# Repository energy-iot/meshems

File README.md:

# MeshEMS Hardware

All files and documentation related to the MeshEMS hardware.

## Overview

The **NESL 865B EMS board** pairs an ESP32-S3 N16R8 (dual-core LX7, 16 MB flash, 8 MB PSRAM) with a purpose-built AC metering add-on and peripherals stack (Ethernet, SD Card reader, OLED display). For energy metering applications it supports either Modbus RTU energy meters (DDS238, CHD130, DDSU666 single-phase) or the CircuitSetup ATM90E32 6-channel SPI meter for 3-phase / multi-CT sites, in addition to the SHT20 temp/humidity sensor which communicates via Modbus. An optional external I2C PCF8574 8-channel SSR bank provide load-control outputs.

## Table of Contents

- [Board Diagrams](#board-diagrams)
- [Hardware Overview](#hardware-overview)
  - [Core Specifications](#core-specifications)
  - [RS-485 MODBUS RTU Module](#hw-519-breakout-rs-485-modbus-rtu-module)
  - [CANBUS V2.0 Interface](#mcp2515-breakout---canbus-v20-interface)
  - [Additional Communication Options](#additional-communication-options)
  - [Input/Output Capabilities](#inputoutput-capabilities)
  - [Power Supply Options](#power-supply-options)
  - [Physical Specifications](#physical-specifications)
- [Board Revisions](#board-revisions)
- [Bill of Materials](#bill-of-materials)
- [Related Repositories](#related-repositories)
- [Contributing](#contributing)
- [License](#license)
- [Safety Disclaimer](#safety-disclaimer)
- [Maintainers](#maintainers)

## Board Diagrams

### NESL 865B EMS Board

### NESL 865B EMS Board — with CircuitSetup ATM90E32 6-Channel Meter

### Legacy MeshEMS Board (V001) built in 2025

## Hardware Overview

### Core Specifications
- **Processor:** Xtensa® dual-core 32-bit LX7 microprocessor, up to 240 MHz
- **Memory:** 16MB Flash + 8MB PSRAM (N16R8 variant)
- **Connectivity:** Wi-Fi 802.11 b/g/n and Bluetooth 5 (LE)
- **USB:** USB OTG interface with Type-C connector
- **GPIO:** 45 programmable GPIO pins
- **Dimensions:** 51mm x 25.5mm x 10mm
- **Operating Voltage:** 3.3V
- **Datasheet:** [ESP32S3 Technical Reference Manual](https://www.espressif.com/sites/default/files/documentation/esp32-s3_technical_reference_manual_en.pdf)
- **Development Board Datasheet:** [ESP32S3-DevKitC-1 Datasheet](https://docs.espressif.com/projects/esp-dev-kits/en/latest/esp32s3/esp32-s3-devkitc-1/index.html)

### HW-519 Breakout RS-485 MODBUS RTU Module
- Industry-standard RS-485 interface for MODBUS RTU communication
- Built-in transceiver with automatic direction control
- 3-pin screw terminal for easy connection (A, B, GND)
- Supports baud rates up to 115200 bps
- **Operating voltage:** 5V (level-shifted from ESP32-S3 at 3.3V)
- **Module Datasheet:** [RS-485 Transceiver Datasheet](https://www.analog.com/media/en/technical-documentation/data-sheets/MAX1487-MAX491.pdf)

### MCP2515 Breakout - CANBUS V2.0 Interface
- CAN 2.0B compliant controller and transceiver
- Supports standard (11-bit) and extended (29-bit) identifiers
- Maximum bitrate: 1 Mbit/s
- Screw terminals for CANH and CANL connections
- Integrated termination resistors (jumper selectable)
- **Controller Datasheet:** [MCP2515 CAN Controller](https://ww1.microchip.com/downloads/en/DeviceDoc/MCP2515-Stand-Alone-CAN-Controller-with-SPI-20001801J.pdf)
- **Transceiver Datasheet:** [TJA1051 CAN Transceiver](https://www.nxp.com/docs/en/data-sheet/TJA1051.pdf)

### Additional Communication Options
- **BLE/BLE Mesh:** Utilizing ESP32S3's built-in Bluetooth capabilities

### Input/Output Capabilities
- **Button Array Interface:** Analog input with voltage divider network
- **Display:** Optional 1.3" OLED display (SPI interface)

### Power Supply Options
- **USB Power:** 5V via USB Type-C connector
- **DC Power:** 5VDC via screw terminals to on board, connects directly to 5VIN of ESP32 (5V input MAX).

**Not UL/CE Certified for AC Applications:** This development kit by itself is NOT certified for direct connection to AC mains.

### Physical Specifications
- PCB Dimensions: 150mm x 90mm (main board)
- Mounting: 4x M3 mounting holes (3.2mm diameter)

---
## Board Revisions

| Revision | Year | Status | Diagram |
| --- | --- | --- | --- |
| NESL 865B | 2026 | Current | [Board diagram](docs/images/NESL%20865B_EMS_Board_Diagram.jpg) |
| MeshEMS V001 | 2025 | Legacy | [Board diagram](docs/images/ems_board_pinout_V001.png) |

## Bill of Materials

Bill of Materials files live in [`bom/`](bom/):

| File | Format | Notes |
| --- | --- | --- |
| [MeshEMS V3 BOM (w/o CS Energy Meter)](bom/20260716_MeshEMS_V3_BOM_woCSEnergyMeter%20-%20BOM.csv) | CSV | Compatible with NESL EMS Controller PCB 865B |
| [MeshEMS V3 BOM (w/o CS Energy Meter)](bom/20260716_MeshEMS_V3_BOM_woCSEnergyMeter.xlsx) | XLSX | Source spreadsheet; `Boards to build` drives extended quantities |

## Related Repositories

- [energy-iot/meshems-openami-metering](https://github.com/energy-iot/meshems-openami-metering) — firmware that runs on this hardware (ESP32-S3 / PlatformIO)
- [energy-iot/docs](https://github.com/energy-iot/docs) — platform documentation

## Contributing

Contributions to the hardware design, BOM, and documentation are welcome.

1. Fork the repository and create a feature branch.
2. Make your changes (board files, BOM updates, docs).
3. Sign your commits with `git commit -s`.
4. Open a pull request describing the change and the board revision it targets.

For broader context and integration ideas, see [energy-iot/docs](https://github.com/energy-iot/docs).

## License

This project is licensed under the [CERN Open Hardware Licence Version 2 – Weakly Reciprocal (CERN-OHL-W-2.0)](LICENSE).

> **Note:** CERN-OHL-W is a weakly reciprocal open-hardware licence. Modifications to
> the covered board design files (schematics, PCB layouts, gerbers) must be shared under
> the same licence, while it allows those design files to be combined with separately
> licensed components. See the [CERN-OHL FAQ](https://ohwr.org/project/cernohl/wikis/Documents/CERN-OHL-version-2)
> for details.

## Safety Disclaimer

⚠️ **This hardware connects to AC mains voltage.** It is **NOT UL/CE certified** for direct
connection to AC mains. AC power connections must be installed by a qualified electrician in
accordance with local electrical codes, mounted in an appropriate non-conductive enclosure,
with proper grounding and circuit protection. Always disconnect power before servicing.

**Failure to follow proper electrical safety practices could result in severe electric shock,
fire, serious injury, or death.**

## Maintainers

Maintained by the [energy-iot](https://github.com/energy-iot) organization.

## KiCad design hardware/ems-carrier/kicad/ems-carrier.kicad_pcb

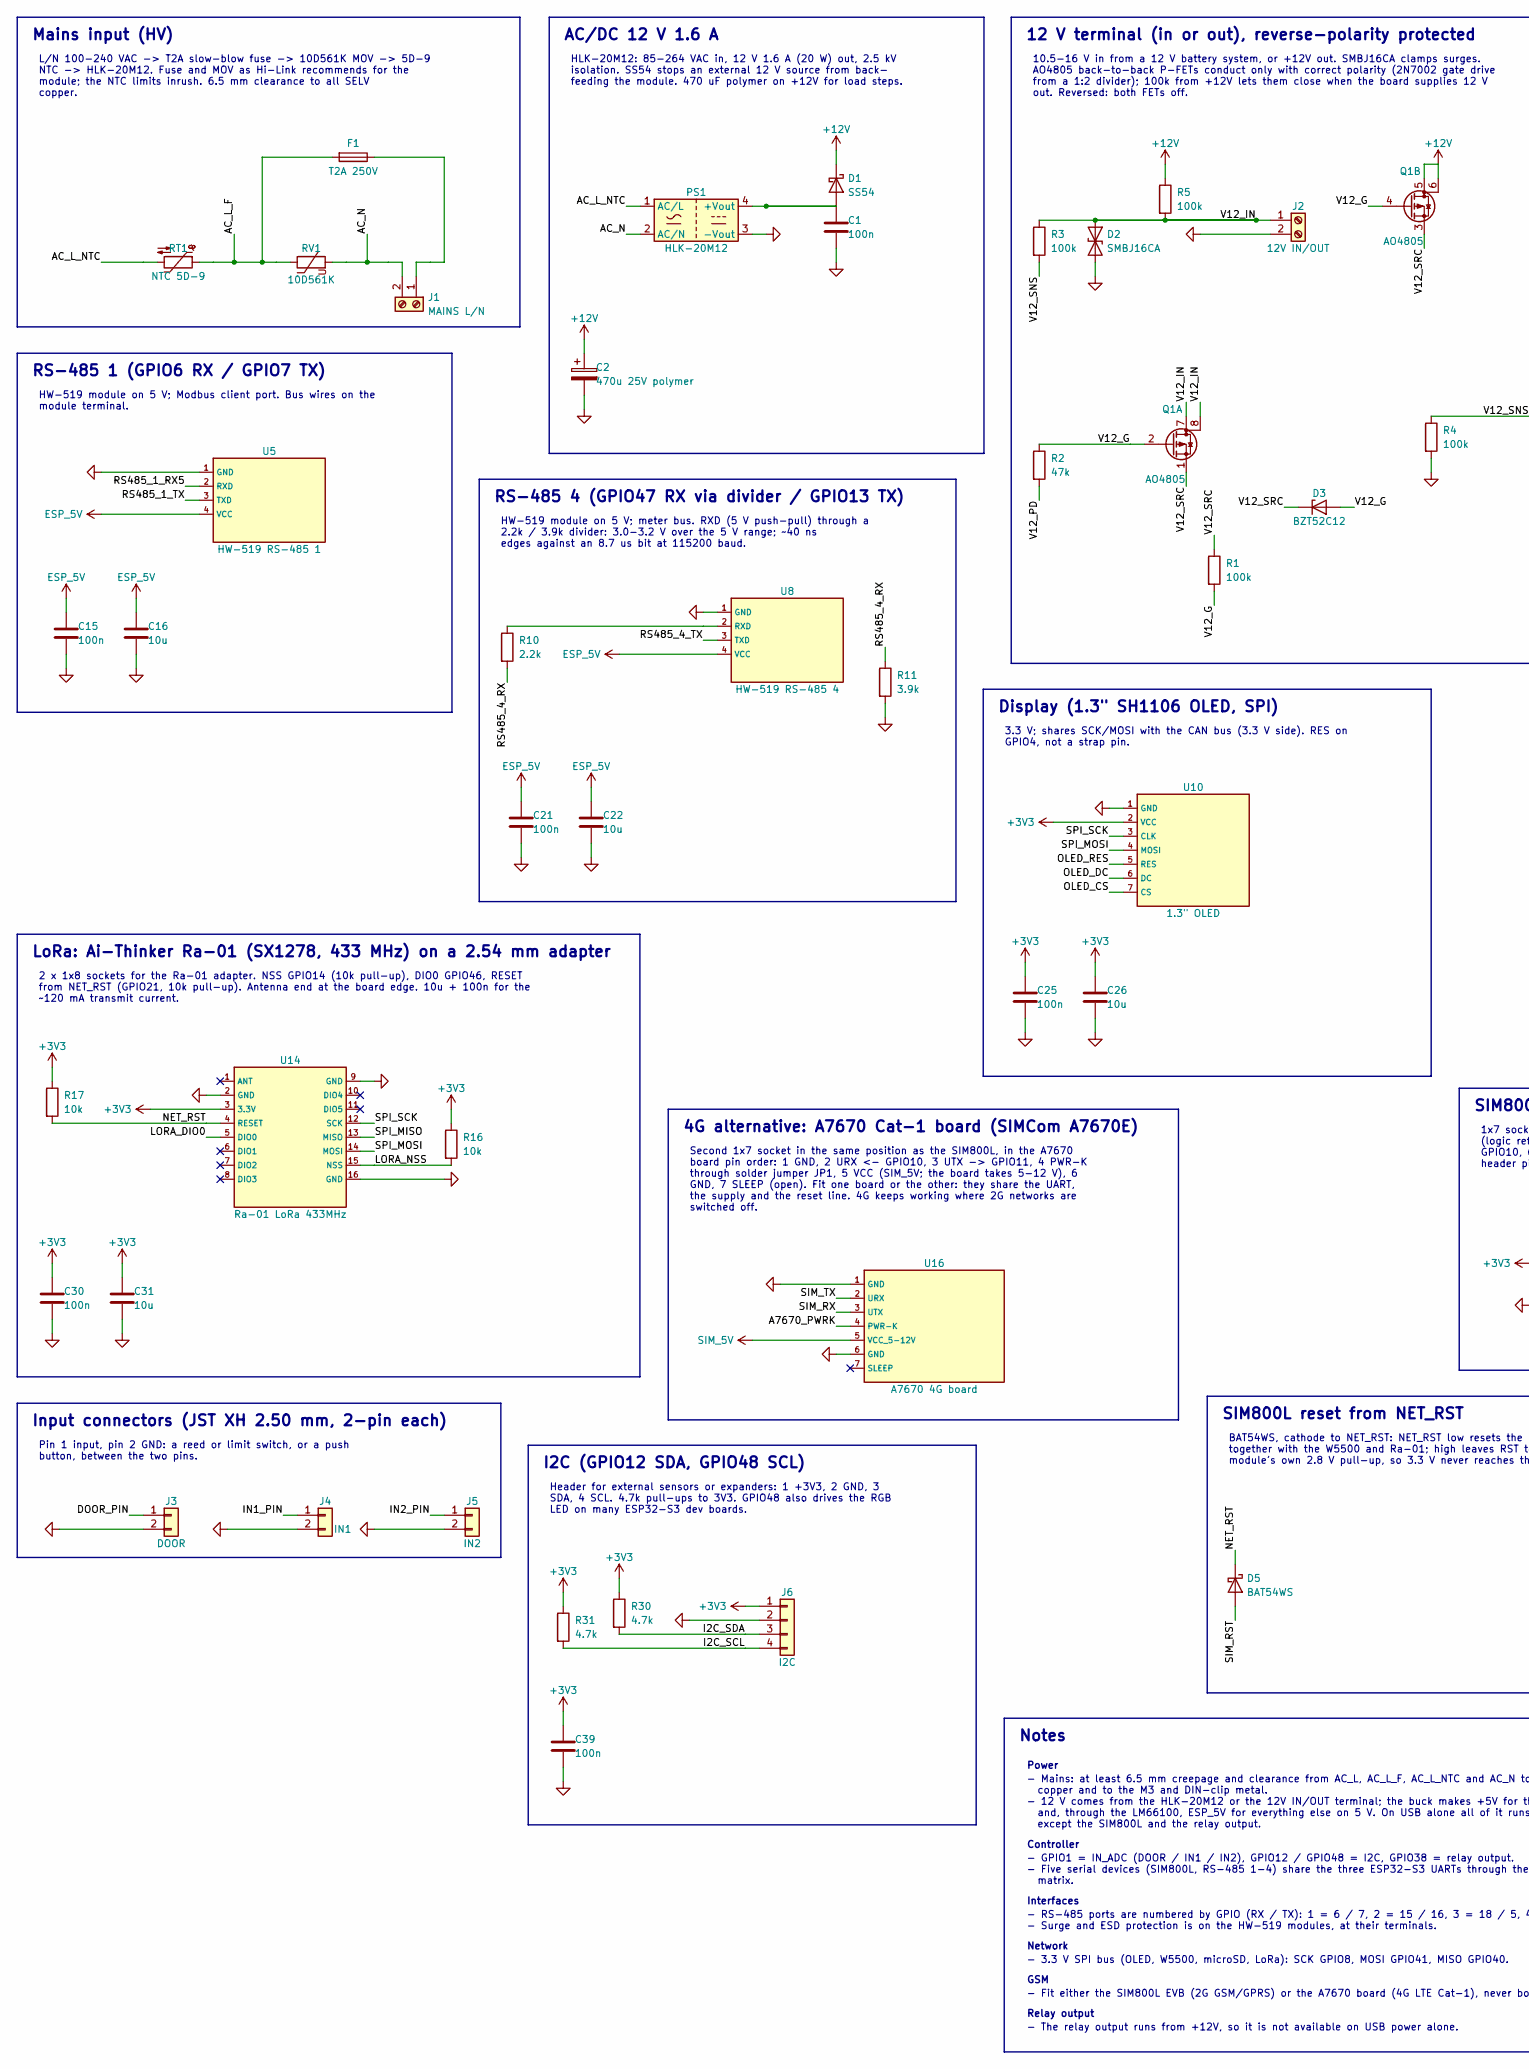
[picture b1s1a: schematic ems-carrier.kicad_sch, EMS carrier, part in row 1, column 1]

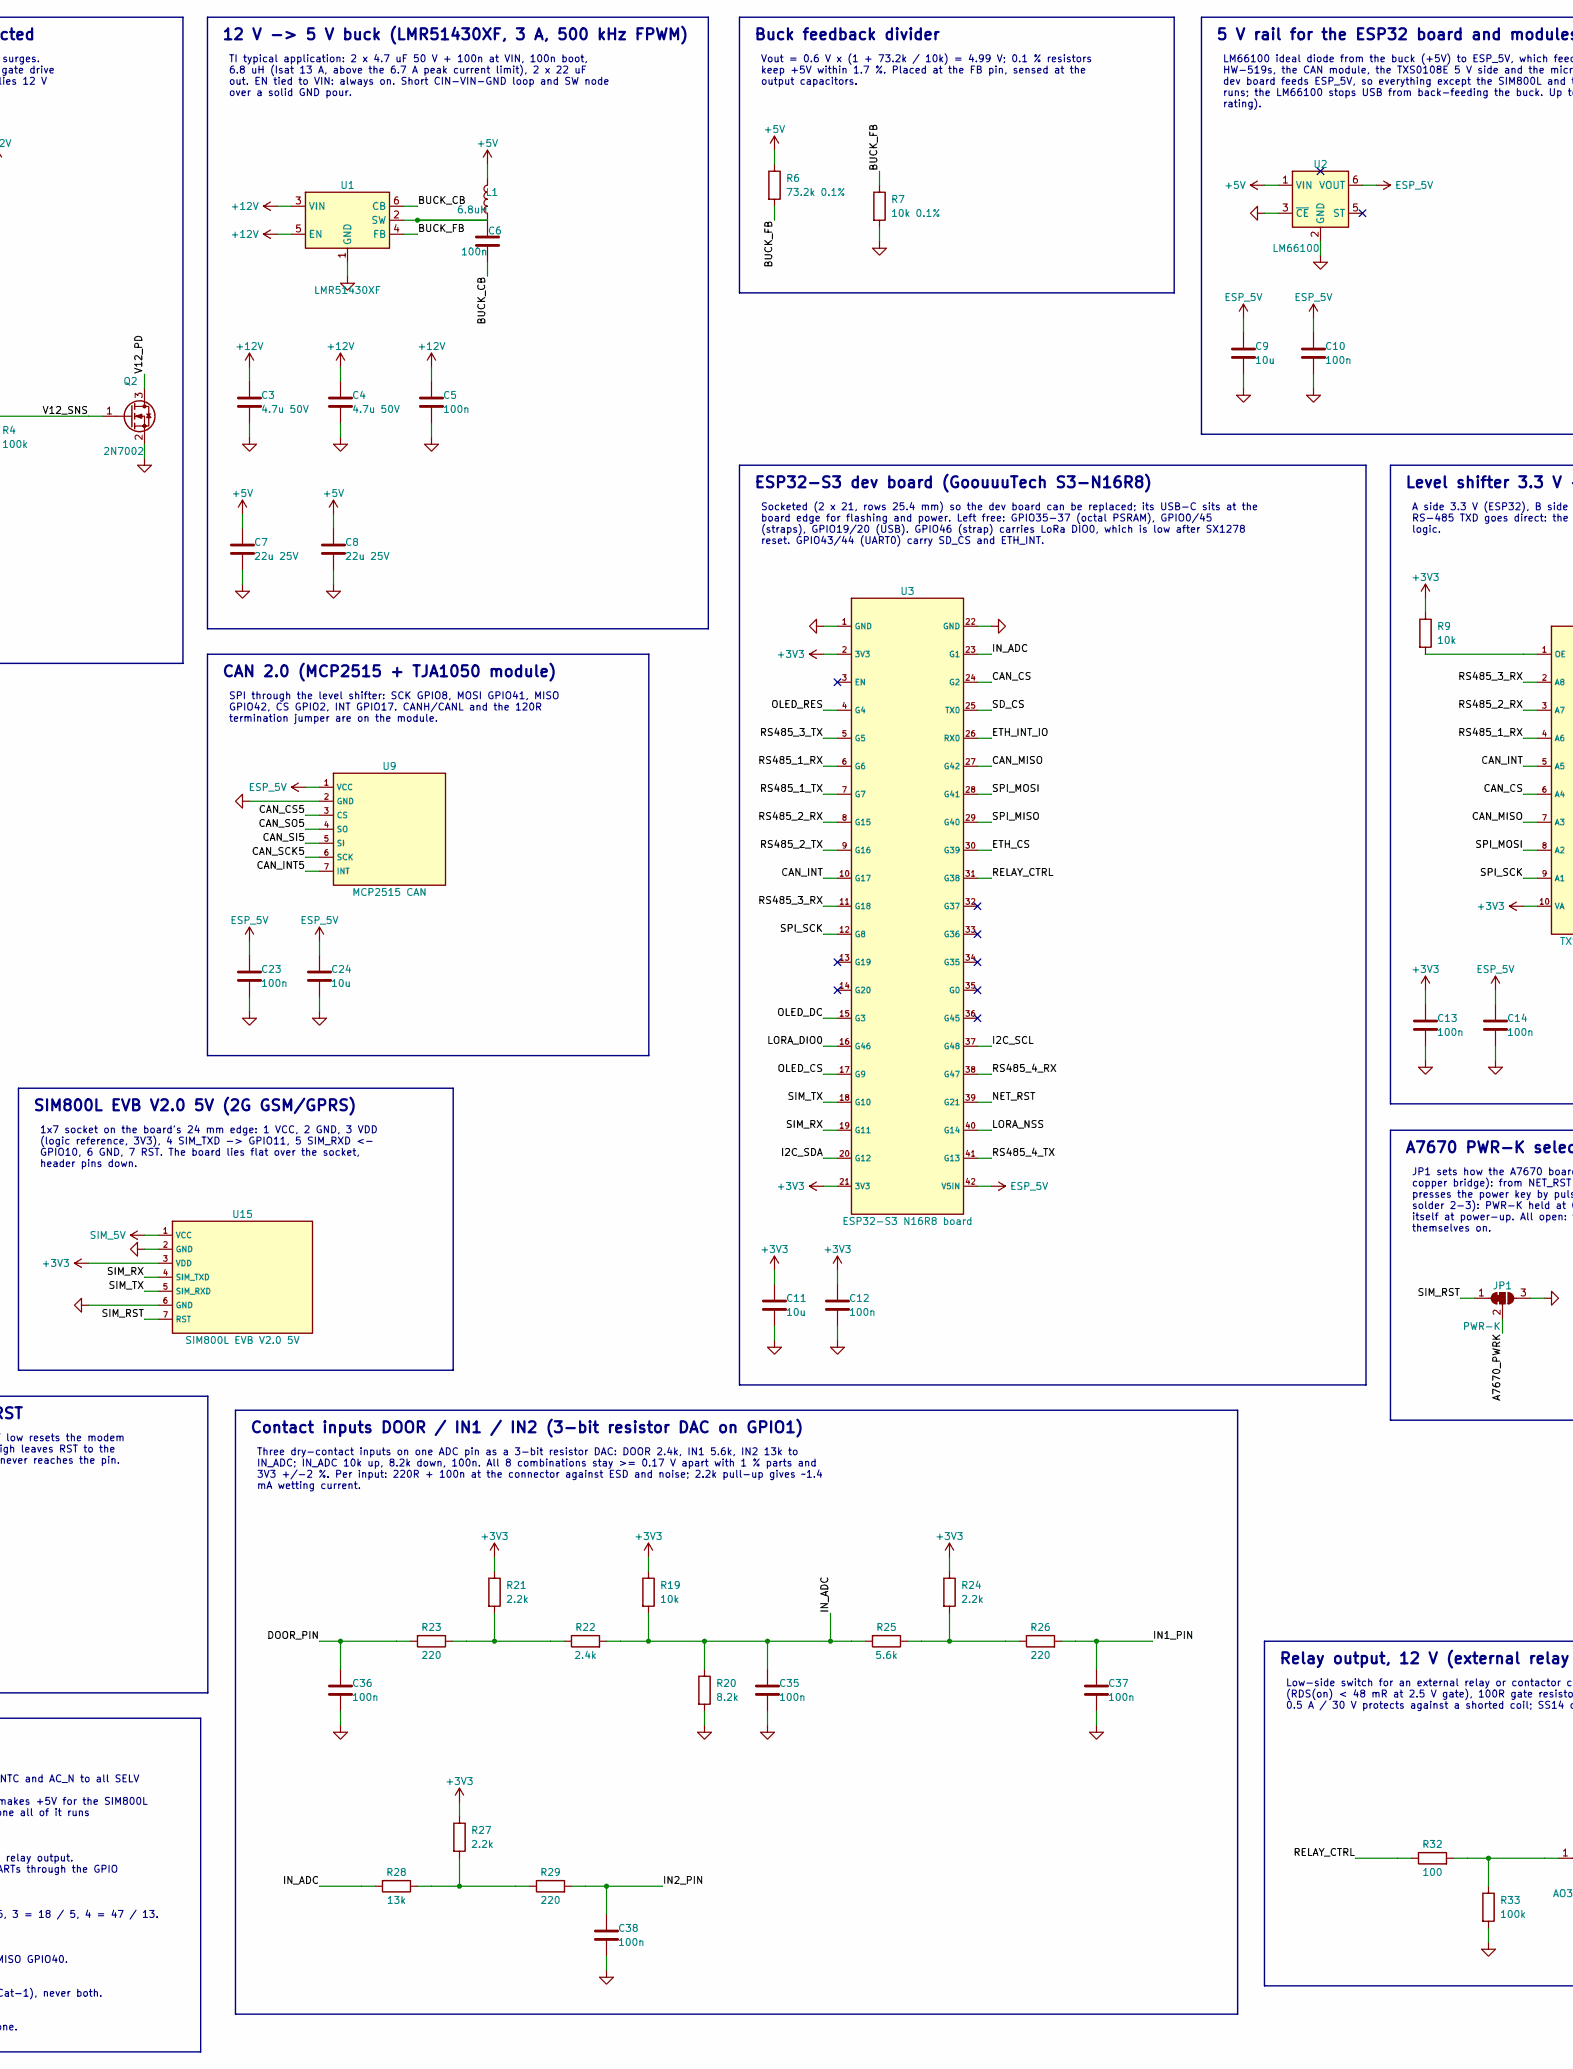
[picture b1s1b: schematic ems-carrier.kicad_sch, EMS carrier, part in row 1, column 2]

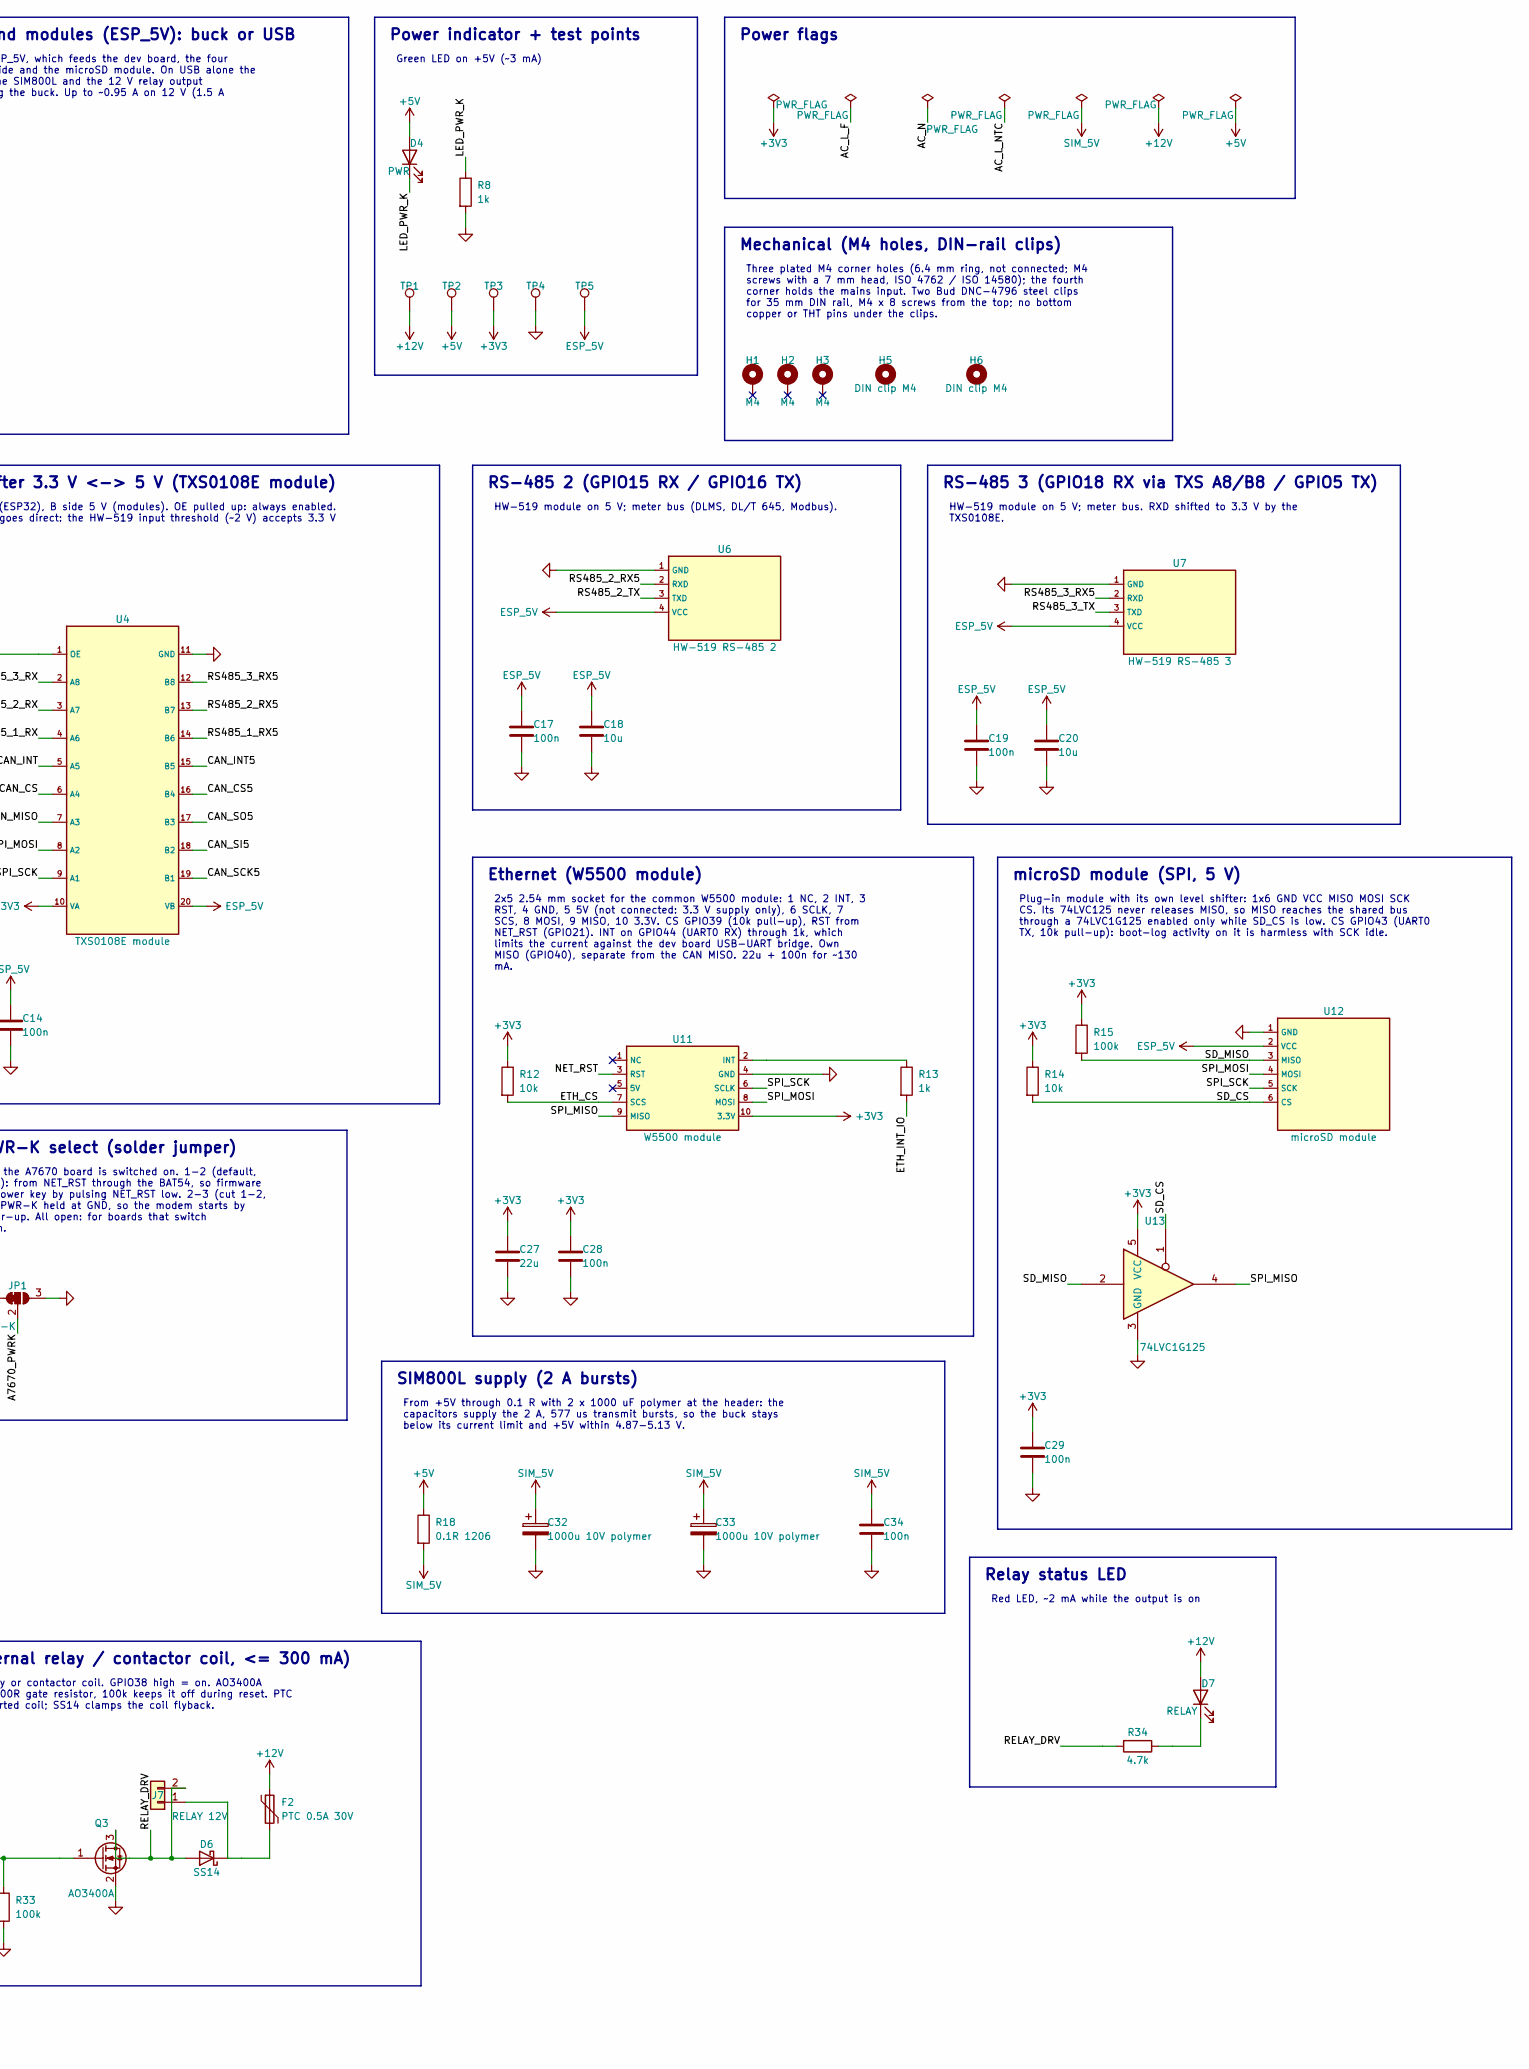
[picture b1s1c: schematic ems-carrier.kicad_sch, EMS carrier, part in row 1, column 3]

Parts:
C1, C5, C6, C10, C12, C13, C14, C15, C17, C19, C21, C23, C25, C28, C29, C30, C34, C35, C36, C37, C38, C39: 100n; C_0603_1608Metric; LCSC C14663
C2: 470u 25V polymer; CP_Elec_8x10; MPN jieerrui MA25V470M8x10 (polymer, 25 mR); LCSC C46550466
C3, C4: 4.7u 50V; C_1206_3216Metric; LCSC C29823
C7, C8: 22u 25V; C_1206_3216Metric; LCSC C12891
C9, C11, C16, C18, C20, C22, C24, C26, C31: 10u; C_0603_1608Metric; LCSC C19702
C27: 22u; C_0805_2012Metric; LCSC C45783
C32, C33: 1000u 10V polymer; CP_Radial_D8.0mm_P3.50mm; MPN jieerrui PA10V1000M8X11 (polymer, 14 mR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; LCSC C49232899
D1: SS54; D_SMA; LCSC C22452
D2: SMBJ16CA; D_SMB; LCSC C113990
D3: BZT52C12; D_SOD-123; LCSC C173429
D4: PWR; LED_0603_1608Metric; LCSC C12624
D5: BAT54WS; D_SOD-323; LCSC C3040452
D6: SS14; D_SMA; LCSC C2480
D7: RELAY; LED_0603_1608Metric; LCSC C2286
F1: T2A 250V; Fuse_Littelfuse_372_D8.50mm; MPN Littelfuse 39212000000 (TR5 time-lag 2 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; LCSC C142678
F2: PTC 0.5A 30V; Fuse_1812_4532Metric; MPN RUILON SMD1812P050TF/30 (0.5 A hold, 1 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; LCSC C12559
H1, H2, H3: M4; MountingHole_4.3mm_M4_Pad6.4
H5, H6: DIN clip M4; DIN_Clip_Bud_DNC-4796
J1: MAINS L/N; TerminalBlock_Phoenix_MKDS-1,5-2-5.08_1x02_P5.08mm_Horizont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; LCSC C474952
J2: 12V IN/OUT; TerminalBlock_Phoenix_MKDS-1,5-2-5.08_1x02_P5.08mm_Horizont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; LCSC C474952
J3: DOOR; JST_XH_B2B-XH-A_1x02_P2.50mm_Vertical; MPN JST B2B-XH-A(LF)(SN); LCSC C158012
J4: IN1; JST_XH_B2B-XH-A_1x02_P2.50mm_Vertical; MPN JST B2B-XH-A(LF)(SN); LCSC C158012
J5: IN2; JST_XH_B2B-XH-A_1x02_P2.50mm_Vertical; MPN JST B2B-XH-A(LF)(SN); LCSC C158012
J6: I2C; JST_XH_B4B-XH-A_1x04_P2.50mm_Vertical; MPN JST B4B-XH-A(LF)(SN); LCSC C144395
J7: RELAY 12V; JST_XH_B2B-XH-A_1x02_P2.50mm_Vertical; MPN JST B2B-XH-A(LF)(SN); LCSC C158012
JP1: PWR-K; SolderJumper-3_P1.3mm_Bridged12_RoundedPad1.0x1.5mm
L1: 6.8uH; L_PROD_PSPMAA0805; MPN PROD PSPMAA0805-6R8M-ANP (19 mR, Isat 1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; LCSC C2962884
PS1: HLK-20M12; Converter_ACDC_HLK-20Mxx; LCSC C465408
Q1: AO4805; SOIC-8_3.9x4.9mm_P1.27mm; LCSC C5183840
Q2: 2N7002; SOT-23; LCSC C8545
Q3: AO3400A; SOT-23; LCSC C20917
R1, R3, R4, R5, R15, R33: 100k; R_0603_1608Metric; LCSC C25803
R2: 47k; R_0603_1608Metric; LCSC C25819
R6: 73.2k 0.1%; R_0603_1608Metric; LCSC C862276
R7: 10k 0.1%; R_0603_1608Metric; LCSC C95204
R8, R13: 1k; R_0603_1608Metric; LCSC C21190
R9, R12, R14, R16, R17, R19: 10k; R_0603_1608Metric; LCSC C25804
R10, R21, R24, R27: 2.2k; R_0603_1608Metric; LCSC C4190
R11: 3.9k; R_0603_1608Metric; LCSC C23018
R18: 0.1R 1206; R_1206_3216Metric; MPN UNI-ROYAL 1206W4F100LT5E (0.25 W); LCSC C25334
R20: 8.2k; R_0603_1608Metric; LCSC C25981
R22: 2.4k; R_0603_1608Metric; LCSC C22940
R23, R26, R29: 220; R_0603_1608Metric; LCSC C22962
R25: 5.6k; R_0603_1608Metric; LCSC C23189
R28: 13k; R_0603_1608Metric; LCSC C22797
R30, R31, R34: 4.7k; R_0603_1608Metric; LCSC C23162
R32: 100; R_0603_1608Metric; LCSC C22775
RT1: NTC 5D-9; RV_Disc_D12mm_W4.4mm_P7.5mm; MPN Hongzhi 5D-9 (5 R, 3 A, 9 mm disc, P 7.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; LCSC C332361
RV1: 10D561K; RV_Disc_D12mm_W4.4mm_P7.5mm; LCSC C2839517
TP1: +12V; TestPoint_Pad_D2.0mm
TP2: +5V; TestPoint_Pad_D2.0mm
TP3: +3V3; TestPoint_Pad_D2.0mm
TP4: GND; TestPoint_Pad_D2.0mm
TP5: ESP_5V; TestPoint_Pad_D2.0mm
U1: LMR51430XF; SOT-23-6; LCSC C5219260
U2: LM66100; SOT-363_SC-70-6; LCSC C2869734
U3: ESP32-S3 N16R8 board; ESP32-S3_DevBoard_2x21_W25.4mm
U4: TXS0108E module; TXS0108E_Module_2x10_W12.7mm
U5: HW-519 RS-485 1; HW-519_RS485_Module_1x4
U6: HW-519 RS-485 2; HW-519_RS485_Module_1x4
U7: HW-519 RS-485 3; HW-519_RS485_Module_1x4
U8: HW-519 RS-485 4; HW-519_RS485_Module_1x4
U9: MCP2515 CAN; MCP2515_CAN_Module_1x7
U10: 1.3" OLED; OLED_1.3in_SPI_1x7
U11: W5500 module; W5500_Module_2x05; LCSC C32713306
U12: microSD module; microSD_Module_1x6
U13: 74LVC1G125; SOT-353_SC-70-5; LCSC C52140430
U14: Ra-01 LoRa 433MHz; Ra-01_Adapter_2x1x8_W20.32mm
U15: SIM800L EVB V2.0 5V; SIM800L_EVB_1x7
U16: A7670 4G board; A7670_4G_Board_1x7

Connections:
+3V3: C11.1, C12.1, C13.1, C25.1, C26.1, C27.1, C28.1, C29.1, C30.1, C31.1, C39.1, J6.1, R9.1, R12.1, R14.1, R15.1, R16.1, R17.1, R19.1, R21.1, R24.1, R27.1, R30.1, R31.1, TP3.1, U3.2 (3V3), U3.21 (3V3), U4.10 (VA), U10.2 (VCC), U11.10 (3.3V), U13.5 (VCC), U14.3 (3.3V), U15.3 (VDD)
+5V: C7.1, C8.1, D4.2 (A), L1.2, R6.1, R18.1, TP2.1, U2.1 (VIN)
+12V: C2.1, C3.1, C4.1, C5.1, D1.1 (K), D7.2 (A), F2.1, Q1.5 (D), Q1.6 (D), R5.1, TP1.1, U1.3 (VIN), U1.5 (EN)
/A7670_PWRK: JP1.2 (C), U16.4 (PWR-K)
/AC_L_F: F1.2, RT1.1, RV1.1
/AC_L_NTC: PS1.1 (AC/L), RT1.2
/AC_N: J1.2, PS1.2 (AC/N), RV1.2
/BUCK_CB: C6.1, U1.6 (CB)
/BUCK_FB: R6.2, R7.1, U1.4 (FB)
/CAN_CS: U3.24 (G2), U4.6 (A4)
/CAN_CS5: U4.16 (B4), U9.3 (CS)
/CAN_INT: U3.10 (G17), U4.5 (A5)
/CAN_INT5: U4.15 (B5), U9.7 (INT)
/CAN_MISO: U3.27 (G42), U4.7 (A3)
/CAN_SCK5: U4.19 (B1), U9.6 (SCK)
/CAN_SI5: U4.18 (B2), U9.5 (SI)
/CAN_SO5: U4.17 (B3), U9.4 (SO)
/DOOR_PIN: C36.1, J3.1, R23.2
/ETH_CS: R12.2, U3.30 (G39), U11.7 (SCS)
/ETH_INT_IO: R13.2, U3.26 (RX0)
/I2C_SCL: J6.4, R31.2, U3.37 (G48)
/I2C_SDA: J6.3, R30.2, U3.20 (G12)
/IN1_PIN: C37.1, J4.1, R26.2
/IN2_PIN: C38.1, J5.1, R29.2
/IN_ADC: C35.1, R19.2, R20.1, R22.2, R25.2, R28.2, U3.23 (G1)
/LED_PWR_K: D4.1 (K), R8.1
/LORA_DIO0: U3.16 (G46), U14.5 (DIO0)
/LORA_NSS: R16.2, U3.40 (G14), U14.15 (NSS)
/NET_RST: D5.1 (K), R17.2, U3.39 (G21), U11.3 (RST), U14.4 (RESET)
/OLED_CS: U3.17 (G9), U10.7 (CS)
/OLED_DC: U3.15 (G3), U10.6 (DC)
/OLED_RES: U3.4 (G4), U10.5 (RES)
/RELAY_CTRL: R32.1, U3.31 (G38)
/RELAY_DRV: D6.2 (A), J7.2, Q3.3 (D), R34.2
/RS485_1_RX: U3.6 (G6), U4.4 (A6)
/RS485_1_RX5: U4.14 (B6), U5.2 (RXD)
/RS485_1_TX: U3.7 (G7), U5.3 (TXD)
/RS485_2_RX: U3.8 (G15), U4.3 (A7)
/RS485_2_RX5: U4.13 (B7), U6.2 (RXD)
/RS485_2_TX: U3.9 (G16), U6.3 (TXD)
/RS485_3_RX: U3.11 (G18), U4.2 (A8)
/RS485_3_RX5: U4.12 (B8), U7.2 (RXD)
/RS485_3_TX: U3.5 (G5), U7.3 (TXD)
/RS485_4_RX: R10.2, R11.1, U3.38 (G47)
/RS485_4_TX: U3.41 (G13), U8.3 (TXD)
/SD_CS: R14.2, U3.25 (TX0), U12.6 (CS), U13.1
/SD_MISO: R15.2, U12.3 (MISO), U13.2
/SIM_RST: D5.2 (A), JP1.1 (A), U15.7 (RST)
/SIM_RX: U3.19 (G11), U15.4 (SIM_TXD), U16.3 (UTX)
/SIM_TX: U3.18 (G10), U15.5 (SIM_RXD), U16.2 (URX)
/SPI_MISO: U3.29 (G40), U11.9 (MISO), U13.4, U14.13 (MISO)
/SPI_MOSI: U3.28 (G41), U4.8 (A2), U10.4 (MOSI), U11.8 (MOSI), U12.4 (MOSI), U14.14 (MOSI)
/SPI_SCK: U3.12 (G8), U4.9 (A1), U10.3 (CLK), U11.6 (SCLK), U12.5 (SCK), U14.12 (SCK)
/V12_G: D3.2 (A), Q1.2 (G), Q1.4 (G), R1.2, R2.1
/V12_IN: D2.1 (A1), J2.1, Q1.7 (D), Q1.8 (D), R3.1, R5.2
/V12_PD: Q2.3 (D), R2.2
/V12_SNS: Q2.1 (G), R3.2, R4.1
/V12_SRC: D3.1 (K), Q1.1 (S), Q1.3 (S), R1.1
ESP_5V: C9.1, C10.1, C14.1, C15.1, C16.1, C17.1, C18.1, C19.1, C20.1, C21.1, C22.1, C23.1, C24.1, TP5.1, U2.6 (VOUT), U3.42 (V5IN), U4.20 (VB), U5.4 (VCC), U6.4 (VCC), U7.4 (VCC), U8.4 (VCC), U9.1 (VCC), U12.2 (VCC)
GND: C1.2, C2.2, C3.2, C4.2, C5.2, C7.2, C8.2, C9.2, C10.2, C11.2, C12.2, C13.2, C14.2, C15.2, C16.2, C17.2, C18.2, C19.2, C20.2, C21.2, C22.2, C23.2, C24.2, C25.2, C26.2, C27.2, C28.2, C29.2, C30.2, C31.2, C32.2, C33.2, C34.2, C35.2, C36.2, C37.2, C38.2, C39.2, D2.2 (A2), J2.2, J3.2, J4.2, J5.2, J6.2, JP1.3 (B), PS1.3 (-Vout), Q2.2 (S), Q3.2 (S), R4.2, R7.2, R8.2, R11.2, R20.2, R33.2, TP4.1, U1.1 (GND), U2.2 (GND), U2.3 (~CE), U3.1 (GND), U3.22 (GND), U4.11 (GND), U5.1 (GND), U6.1 (GND), U7.1 (GND), U8.1 (GND), U9.2 (GND), U10.1 (GND), U11.4 (GND), U12.1 (GND), U13.3 (GND), U14.2 (GND), U14.9 (GND), U14.16 (GND), U15.2 (GND), U15.6 (GND), U16.1 (GND), U16.6 (GND)
unnamed: C1.1, D1.2 (A), PS1.4 (+Vout)
unnamed: D6.1 (K), F2.2, J7.1
unnamed: D7.1 (K), R34.1
unnamed: F1.1, J1.1
unnamed: Q3.1 (G), R32.2, R33.1
unnamed: R21.2, R22.1, R23.1
unnamed: R24.2, R25.1, R26.1
unnamed: R27.2, R28.1, R29.1
unnamed: C6.2, L1.1, U1.2 (SW)
unnamed: R9.2, U4.1 (OE)
unnamed: R10.1, U8.2 (RXD)
unnamed: R13.1, U11.2 (INT)
SIM_5V: C32.1, C33.1, C34.1, R18.2, U15.1 (VCC), U16.5 (VCC_5-12V)

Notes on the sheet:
Mains input (HV)
L/N 100-240 VAC -> T2A slow-blow fuse -> 10D561K MOV -> 5D-9 NTC -> HLK-20M12. Fuse and MOV as Hi-Link recommends for the module; the NTC limits inrush. 6.5 mm clearance to all SELV copper.
AC/DC 12 V 1.6 A
HLK-20M12: 85-264 VAC in, 12 V 1.6 A (20 W) out, 2.5 kV isolation. SS54 stops an external 12 V source from back- feeding the module. 470 uF polymer on +12V for load steps.
12 V terminal (in or out), reverse-polarity protected
10.5-16 V in from a 12 V battery system, or +12V out. SMBJ16CA clamps surges. AO4805 back-to-back P-FETs conduct only with correct polarity (2N7002 gate drive from a 1:2 divider); 100k from +12V lets them close when the board supplies 12 V out. Reversed: both FETs off.
12 V -> 5 V buck (LMR51430XF, 3 A, 500 kHz FPWM)
TI typical application: 2 x 4.7 uF 50 V + 100n at VIN, 100n boot, 6.8 uH (Isat 13 A, above the 6.7 A peak current limit), 2 x 22 uF out. EN tied to VIN: always on. Short CIN-VIN-GND loop and SW node over a solid GND pour.
Buck feedback divider
Vout = 0.6 V x (1 + 73.2k / 10k) = 4.99 V; 0.1 % resistors keep +5V within 1.7 %. Placed at the FB pin, sensed at the output capacitors.
5 V rail for the ESP32 board and modules (ESP_5V): buck or USB
LM66100 ideal diode from the buck (+5V) to ESP_5V, which feeds the dev board, the four HW-519s, the CAN module, the TXS0108E 5 V side and the microSD module. On USB alone the dev board feeds ESP_5V, so everything except the SIM800L and the 12 V relay output runs; the LM66100 stops USB from back-fee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
Power indicator + test points
Green LED on +5V (~3 mA)
Power flags
Mechanical (M4 holes, DIN-rail clips)
Three plated M4 corner holes (6.4 mm ring, not connected; M4 screws with a 7 mm head, ISO 4762 / ISO 14580); the fourth corner holds the mains input. Two Bud DNC-4796 steel clips for 35 mm DIN rail, M4 x 8 screws from the top; no bottom copper or THT pins under the clips.
ESP32-S3 dev board (GoouuuTech S3-N16R8)
Socketed (2 x 21, rows 25.4 mm) so the dev board can be replaced; its USB-C sits at the board edge for flashing and power. Left free: GPIO35-37 (octal PSRAM), GPIO0/45 (straps), GPIO19/20 (USB). GPIO46 (strap) carries LoRa DIO0, which is low after SX1278 reset. GPIO43/44 (UART0) carry SD_CS and ETH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
Level shifter 3.3 V <-> 5 V (TXS0108E module)
A side 3.3 V (ESP32), B side 5 V (modules). OE pulled up: always enabled. RS-485 TXD goes direct: the HW-519 input threshold (~2 V) accepts 3.3 V logic.
RS-485 1 (GPIO6 RX / GPIO7 TX)
HW-519 module on 5 V; Modbus client port. Bus wires on the module terminal.
RS-485 2 (GPIO15 RX / GPIO16 TX)
HW-519 module on 5 V; meter bus (DLMS, DL/T 645, Modbus).
RS-485 3 (GPIO18 RX via TXS A8/B8 / GPIO5 TX)
HW-519 module on 5 V; meter bus. RXD shifted to 3.3 V by the TXS0108E.
RS-485 4 (GPIO47 RX via divider / GPIO13 TX)
HW-519 module on 5 V; meter bus. RXD (5 V push-pull) through a 2.2k / 3.9k divider: 3.0-3.2 V over the 5 V range; ~40 ns edges against an 8.7 us bit at 115200 baud.
CAN 2.0 (MCP2515 + TJA1050 module)
SPI through the level shifter: SCK GPIO8, MOSI GPIO41, MISO GPIO42, CS GPIO2, INT GPIO17. CANH/CANL and the 120R termination jumper are on the module.
Display (1.3" SH1106 OLED, SPI)
3.3 V; shares SCK/MOSI with the CAN bus (3.3 V side). RES on GPIO4, not a strap pin.
Ethernet (W5500 module)
2x5 2.54 mm socket for the common W5500 module: 1 NC, 2 INT, 3 RST, 4 GND, 5 5V (not connected: 3.3 V supply only), 6 SCLK, 7 SCS, 8 MOSI, 9 MISO, 10 3.3V. CS GPIO39 (10k pull-up), RST from NET_RST (GPIO21). INT on GPIO44 (UART0 RX) through 1k, which limits the current against the dev board USB-UAR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
microSD module (SPI, 5 V)
Plug-in module with its own level shifter: 1x6 GND VCC MISO MOSI SCK CS. Its 74LVC125 never releases MISO, so MISO reaches the shared bus through a 74LVC1G125 enabled only while SD_CS is low. CS GPIO43 (UART0 TX, 10k pull-up): boot-log activity on it is harmless with SCK idle.
LoRa: Ai-Thinker Ra-01 (SX1278, 433 MHz) on a 2.54 mm adapter
2 x 1x8 sockets for the Ra-01 adapter. NSS GPIO14 (10k pull-up), DIO0 GPIO46, RESET from NET_RST (GPIO21, 10k pull-up). Antenna end at the board edge. 10u + 100n for the ~120 mA transmit current.
SIM800L EVB V2.0 5V (2G GSM/GPRS)

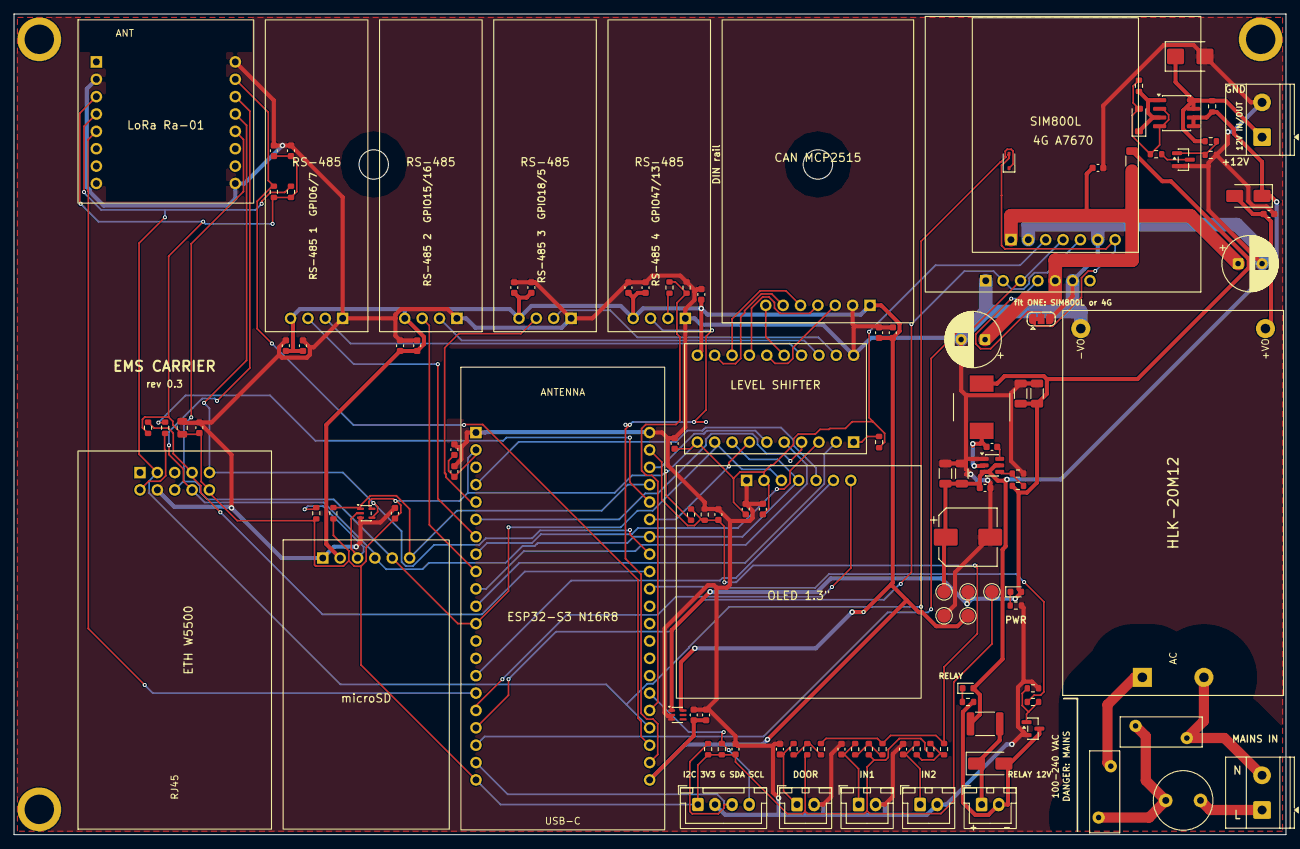
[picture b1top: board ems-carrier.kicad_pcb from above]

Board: 2 copper layers, 186.0 x 120.0 mm, 123 parts (0 on the bottom side), 73 nets.

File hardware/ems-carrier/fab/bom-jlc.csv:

Comment,Designator,Footprint,LCSC Part #
100n,"C1,C5,C6,C10,C12,C13,C14,C15,C17,C19,C21,C23,C25,C28,C29,C30,C34,C35,C36,C37,C38,C39",C_0603_1608Metric,C14663
470u 25V polymer,C2,CP_Elec_8x10,C46550466
4.7u 50V,"C3,C4",C_1206_3216Metric,C29823
22u 25V,"C7,C8",C_1206_3216Metric,C12891
10u,"C9,C11,C16,C18,C20,C22,C24,C26,C31",C_0603_1608Metric,C19702
22u,C27,C_0805_2012Metric,C45783
1000u 10V polymer,"C32,C33",CP_Radial_D8.0mm_P3.50mm,C49232899
SS54,D1,D_SMA,C22452
SMBJ16CA,D2,D_SMB,C113990
BZT52C12,D3,D_SOD-123,C173429
PWR,D4,LED_0603_1608Metric,C12624
BAT54WS,D5,D_SOD-323,C3040452
SS14,D6,D_SMA,C2480
RELAY,D7,LED_0603_1608Metric,C2286
T2A 250V,F1,Fuse_Littelfuse_372_D8.50mm,C142678
PTC 0.5A 30V,F2,Fuse_1812_4532Metric,C12559
MAINS L/N/12V IN/OUT,"J1,J2","TerminalBlock_Phoenix_MKDS-1,5-2-5.08_1x02_P5.08mm_Horizontal",C474952
DOOR...,"J3,J4,J5,J7",JST_XH_B2B-XH-A_1x02_P2.50mm_Vertical,C158012
I2C,J6,JST_XH_B4B-XH-A_1x04_P2.50mm_Vertical,C144395
6.8uH,L1,L_PROD_PSPMAA0805,C2962884
HLK-20M12,PS1,Converter_ACDC_HLK-20Mxx,C465408
AO4805,Q1,SOIC-8_3.9x4.9mm_P1.27mm,C5183840
2N7002,Q2,SOT-23,C8545
AO3400A,Q3,SOT-23,C20917
100k,"R1,R3,R4,R5,R15,R33",R_0603_1608Metric,C25803
47k,R2,R_0603_1608Metric,C25819
73.2k 0.1%,R6,R_0603_1608Metric,C862276
10k 0.1%,R7,R_0603_1608Metric,C95204
1k,"R8,R13",R_0603_1608Metric,C21190
10k,"R9,R12,R14,R16,R17,R19",R_0603_1608Metric,C25804
2.2k,"R10,R21,R24,R27",R_0603_1608Metric,C4190
3.9k,R11,R_0603_1608Metric,C23018
0.1R 1206,R18,R_1206_3216Metric,C25334
8.2k,R20,R_0603_1608Metric,C25981
2.4k,R22,R_0603_1608Metric,C22940
220,"R23,R26,R29",R_0603_1608Metric,C22962
5.6k,R25,R_0603_1608Metric,C23189
13k,R28,R_0603_1608Metric,C22797
4.7k,"R30,R31,R34",R_0603_1608Metric,C23162
100,R32,R_0603_1608Metric,C22775
NTC 5D-9,RT1,RV_Disc_D12mm_W4.4mm_P7.5mm,C332361
10D561K,RV1,RV_Disc_D12mm_W4.4mm_P7.5mm,C2839517
LMR51430XF,U1,SOT-23-6,C5219260
LM66100,U2,SOT-363_SC-70-6,C2869734
W5500 module,U11,W5500_Module_2x05,C32713306
74LVC1G125,U13,SOT-353_SC-70-5,C52140430

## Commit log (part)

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2025-04-03 added display (SH1106 copied to lib); added console; updated pins for SPI OLED; draw rick at boot; add title and overlay to console display
2025-04-03 code cleanup;
2025-04-03 changed relay pin to 18 and swapped modbus 2 module rx/tx pins 15 and 16 to follow same pattern
2025-04-04 added MCP CAN library; loop commented out
2025-04-04 define separate SPI bus for CAN
2025-04-04 enable can on default SPI bus
2025-04-04 comment out loop_can until ready
2025-04-04 updated gitignore with .vscode/extensions.json
2025-04-04 CAN loop set to 5 secs for testinng, improved LOOP, CAN monitor messages
2025-04-04 Improved OLED Messages
2025-04-04 added modbus_client; added ModbusRTUSlave to lib and added debugging - (remove later and fetch dynamically); added setup and loop calls
2025-04-07 rudimentary modbus data model; populate input registers 1 and 2 with temp/humid from sht20
2025-04-08 Working on debugging CAN comms with the MCP2515
2025-04-11 Update README.md
    list some meaningful code challenges for first energy opensource hackathon workshop - April 22-23 2025
2025-04-14 Working MCP CAN updates
2025-04-14 Tweaks to README.md
2025-04-15 Tweaks to CAN operation
    Added the ability to set a flag for read, write, or read/write mode for the CAN interface. Added clearer debugging messages
2025-04-16 Improved comments and new logo bitmap
    Improved comments and overall documentation on modbus_client, can.cpp, data_model
2025-04-16 Added board image to README
2025-04-16 Fixed image link
2025-04-16 Fixed size of image
2025-04-17 MQTT and WiFi initial commit;
2025-04-18 refactor/refine; publish massaged temp/humid to MQTT; prep for EMS workshop WiFi
2025-04-18 wifi: attempt to connect 3 times before failing
2025-04-18 added config (gen device id); move MQTT vars to config
2025-04-18 added lean-in UX of mqtt and button prompt
2025-04-19 Improved docs, IOT logo at splash screen
2025-04-22 Initial commit for EVSE implementation
2025-04-22 addeed DDS238 meter
2025-04-23 Case sensitivity matters
2025-04-23 remove upper-case filenames
2025-04-23 Change the case of the files using a computer with a case sensitive filesystem
2025-04-23 Read all power meter values (untested)
2025-04-23 Corrected return data type and adjusted scales
2025-04-23 Working Sol-Ark Master Polling
2025-04-23 Initial release, untested
2025-04-23 Unit corrections for PowerData
2025-04-23 Add graph to screen and python plotter for pc
2025-04-23 Add sunspec model 213 json serialization
2025-04-23 Integrate rebase into graph
2025-04-23 progress?
2025-04-23 Quick hacks for presentation version that pushes to MQTT
2025-04-24 Working Common Model 1 Sunspec!
2025-05-05 Update README to reflect 120/240 VAC 50/60 hz supply options
2025-05-08 untested 701 block
2025-05-08 SHT20 to MQTT Inital release
2025-05-14 expand for support 3 phase streetpoleEMS subpanel 1-4 tenants per phase
2025-05-14 cleanup code comments and point to shiftr.io mqtt broker, turn on mqtt debug via build bool
2025-05-14 simple oled display update, TODO code comments
2025-05-15 minor updates
2025-05-16 an openami mqtt topic and subtopic formating iteration still iterations to go
2025-05-17 added leakage data model to openami , corrected EMS deviceid to the unique per ESP32S3 8 MAC octets
2025-05-18 added Sunspec model 1 for StreetPoleEMS subpanel nameplate mfr details, and some subtopic naming cleanups
2025-05-18 prep work to split out Harmonics as its own openami mqtt subtopic via Sunspecmodel213 needs splitting first here
2025-05-19 generateDeviceID tweak: use top 4 bytes of EfuseMac
2025-05-20 more ID fixes....ugh
2025-05-23 Draft implemention of model 713
2025-05-24 Initial commit - not working
2025-05-24 Rewrite of EVSE controller implementation (untested)
2025-05-24 Fixed typo in data_model
2025-05-24 Working MQTT publish
2025-05-26 updates to values
2025-05-27 fixed modbus naming convention in files and function names
2025-06-06 Tweaked OLED text display
2025-06-10 wifi updates to default to EMSLab SSID
2025-06-10 expanding openami to include harmonics as own subtopic and loop over all tenant meters each with own suptopic using sunspec model 11, also add sunspec model 1 manufacturer details of ems subpanel hw 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
2025-06-10 test commit
2025-06-10 fix power data cache operations additions to compile/build then will iteerate to use shared cache between modbus pols and mqtt publish differing operational run time frames
2025-06-10 quick fixes for merge and build errors
2025-06-10 powerdata cache updated
2025-06-10 add 'current' reading of meter 1 to history for plotting; print data to serial
2025-06-11 Changed upload speed and wifi setup
2025-06-11 per tenant single phase meter topic subloop added in mqtt report - 3 phase subpanel , can do 3 tenants per phase or 9 tenants per subpanel
2025-06-11 accept the merged data_model.h
2025-06-12 fixed warnings in DTMPowerCache - building mains metering option, also added new meter type CHINT CHD130 - still needs CHD130 register spec to map exact register address map
2025-06-15 OPENAMI mqtt publish extended with 2 more subtopics for subpanel_MFR as Sunspec model 1 schema and subpanel_ENV for temp/humid and door contact/subpanel tamper , also corrected per tenant meter_n sub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
2025-06-16 update to allow modbus poll vs mqtt publish to run at different loop rates in seconds, config.h and deafult in config.cpp BUT TODO intent is let Linux java policy server set this by remote mqtt cmd p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
2025-06-17 updated Modbus poll vs MQTT publish configurable periods - 1 sec modbus, 30 second mqtt publish root period. TODO is adaptive per MQTT subtopic periods. publish at 5/15 min itervals unless a "meaniin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
2025-06-17 added Harmonics to OPENAMI subtopic Publish as its own subtopic - covered under advanced Sunspec model 213
2025-06-19 stats report on bps bandwidth usage added to openami every 5 mins
2025-06-20 corrected ModbusMaster_pollrate typo missed this edit to 2 classes on last stats code update
2025-06-20 oled friendly stuff
2025-07-07 Update README.md
    add SSR spec sheet link details and optional OPENAMI over MQTT highlights
2025-07-07 Update README.md
    added link for 7 pin 1.3 inch oled display
2025-07-14 Update README.md
    Renamed repository to meshems.
2025-07-26 First Porting --untested--
2025-07-29 tweaks to gitignore
2025-08-01 support multiple cabinet meters, 1-n , and cabinet temp/humid sensor on same rs485 maser port- note stage temp/humid to nodenum 99 add geo coordinates of subpanel in OPENAMI _ENV JSON BLOB portion
2025-08-01 updated some registers
2025-08-06 Update README.md
    Added URL to the Open AMI schema
2025-08-06 Remove C program files
2025-08-06 Implementation of second 701 model for Load port, Implements Model 714
2025-08-09 Updates to mdoel definitions
2025-08-09 Housekeeping
2025-08-09 updates to file structure
2025-08-09 fix pymodbus dependency issue
2025-08-09 fix to pymodbus
2025-08-09 Fix to ModbusSlaveContext
2025-08-09 second pass fix to pymodbus
2025-08-09 3rd fix to pymodbus
2025-08-09 fixes to pymodbus
2025-08-09 another commit
2025-08-09 updates to slave parameter
2025-08-09 pymodbus
2025-08-09 fixes to server
2025-08-09 changed to slave_id
2025-08-09 remove slave_id
2025-08-09 removed extra code
2025-08-09 updates to unit ID
2025-08-09 update port
2025-08-09 fix read registers
2025-08-09 change to device_id
2025-08-09 update the rest of the entries
2025-08-09 Working Version. Updated terminal display
2025-08-14 remove legacy code refs
2025-08-14 fixed function reference
2025-08-14 fixed string utf8 error
2025-08-14 fix bug with MnAlarmInfo
2025-08-14 debuging 701
2025-12-22 Update Scorecard workflow permissions and action version
2025-12-22 Add OpenSSF Scorecard badge to README
2025-12-22 Add CodeQL analysis workflow configuration
2025-12-22 Change C/C++ build mode to manual in CodeQL workflow
2025-12-22 Modify build steps for PlatformIO integration
    Updated manual build steps to include PlatformIO installation and project build commands.
2026-03-10 modbus folder
2026-04-22 2026 sf hackathon credentials
2026-04-22 pins definitions and updates for the NESL PCB865B board
2026-04-22 hackathon wifi settings
2026-04-22 openami topic is lower-case, increase publish rate
2026-04-22 button task
2026-04-22 nesldtm meter replaces dds238
2026-04-23 log/publish all dtm registers
2026-04-23 remove button loop
2026-04-23 i2c TwoWire control SSR module
